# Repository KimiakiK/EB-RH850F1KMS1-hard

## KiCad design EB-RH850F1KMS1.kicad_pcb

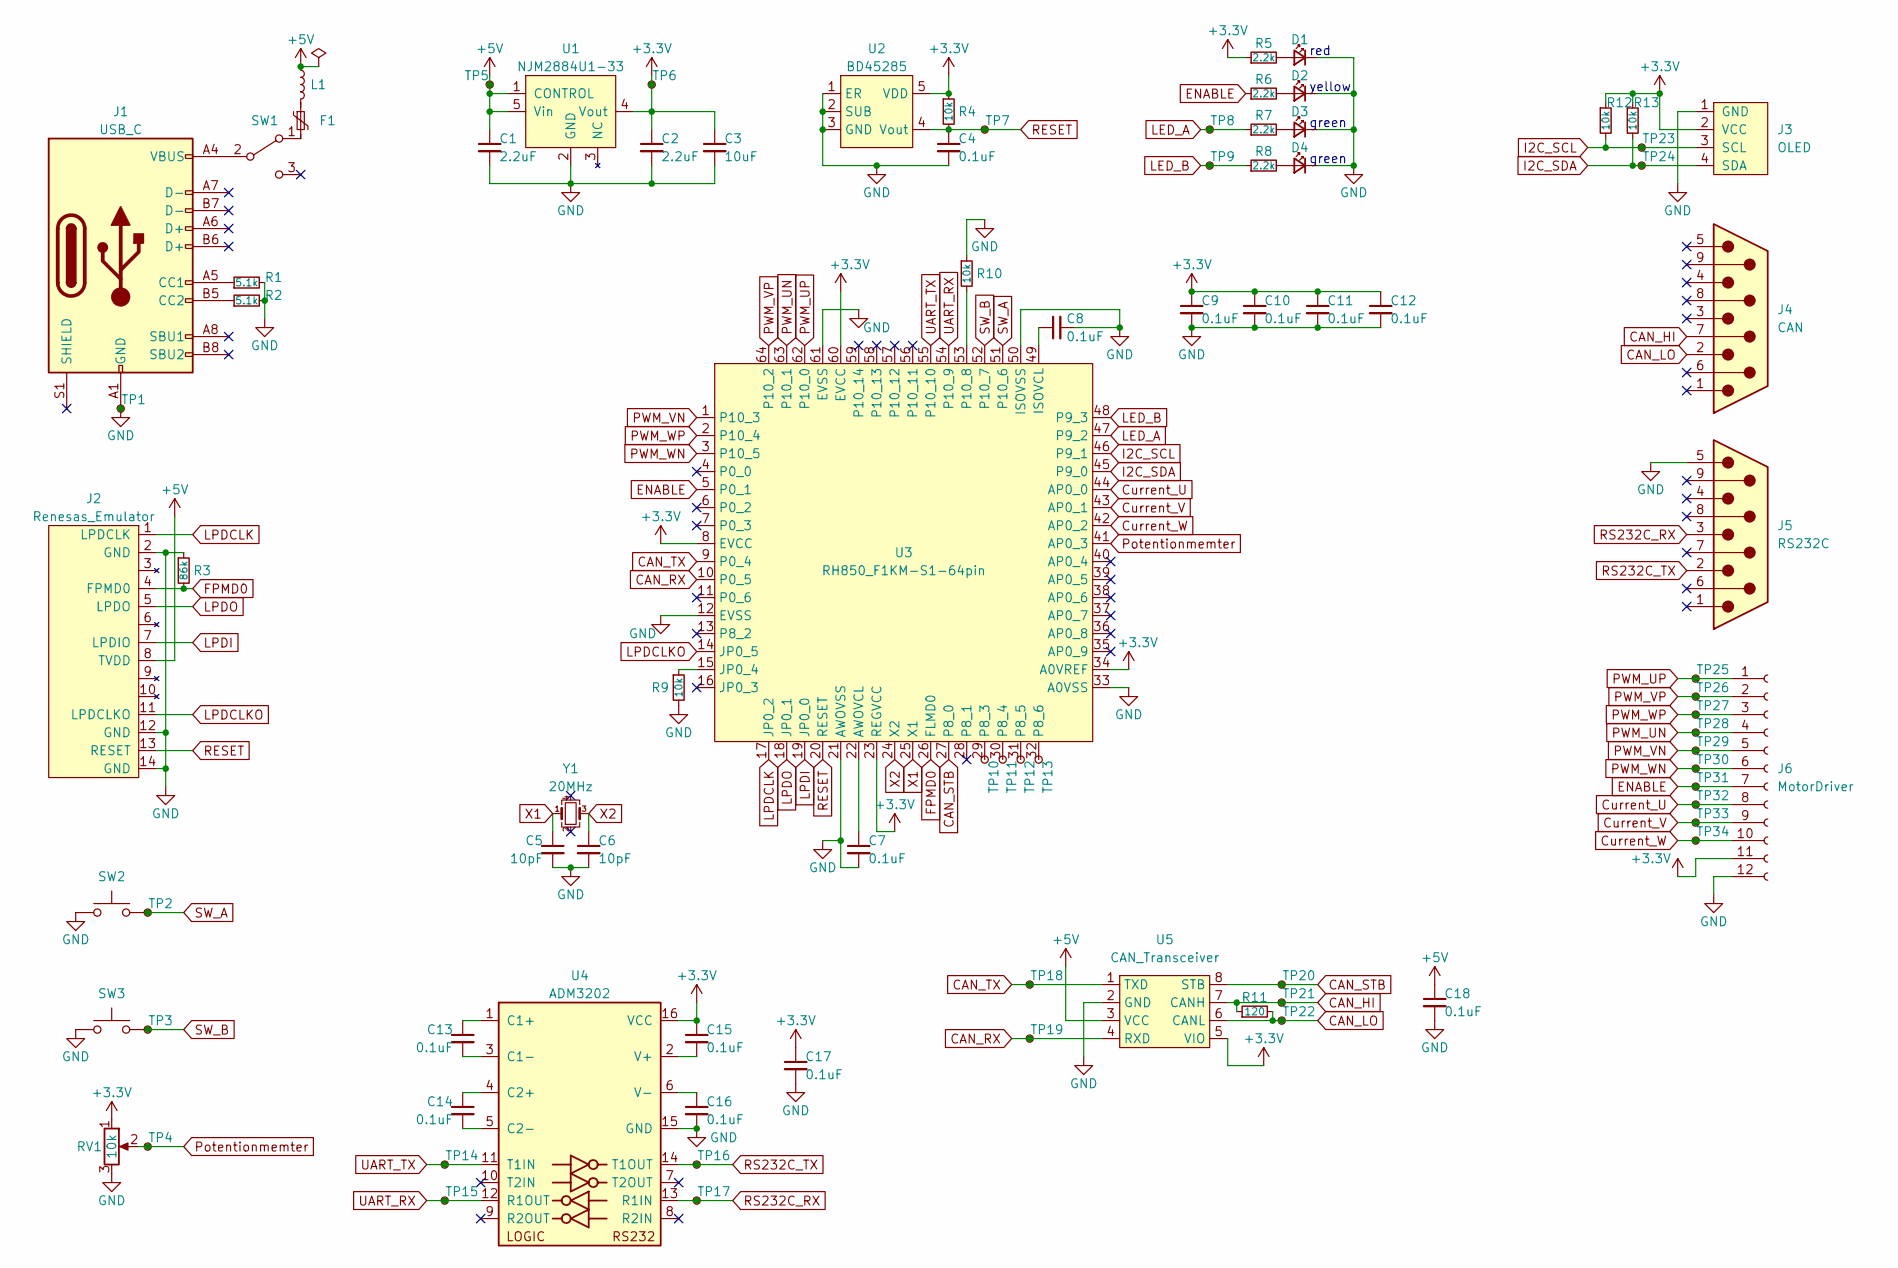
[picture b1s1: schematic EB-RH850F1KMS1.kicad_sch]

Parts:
C1, C2: 2.2uF; 1608Metric
C3: 10uF; 1608Metric
C4, C7, C8, C9, C10, C11, C12, C13, C14, C15, C16, C17, C18: 0.1uF; 1608Metric
C5, C6: 10pF; 1005Metric
D1, D2, D3, D4: LED; 1608Metric
F1: Polyfuse; 1608Metric
J1: USB_C; USB Type-C 5077CR-16SMC2-BK-TR
J2: Renesas_Emulator; IDC-Header_2x07_P2.54mm_Vertical
J3: OLED; OLED_128x64
J4: CAN; DSUB-9_Male_Horizontal_P2.77x2.84mm_EdgePinOffset7.70mm_Hou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
J5: RS232C; DSUB-9_Male_Horizontal_P2.77x2.84mm_EdgePinOffset7.70mm_Hou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
J6: MotorDriver; PinSocket_2x06_P2.54mm_Horizontal
L1: L; 1608Metric
R1, R2: 5.1k; 1608Metric
R3: 86k; 1608Metric
R4, R9, R10, R12, R13: 10k; 1608Metric
R5, R6, R7, R8: 2.2k; 1608Metric
R11: 120; 1608Metric
RV1: 10k; Potentiometer_Alps_RK097_Dual_Horizontal
SW1: SW_SPDT; Toggle_Switch
SW2, SW3: SW_Push; SW_TVAF06
TP1, TP2, TP3, TP4, TP5, TP6, TP7, TP8, TP9, TP10, TP11, TP12, TP13, TP14, TP15, TP16, TP17, TP18, TP19, TP20, TP21, TP22, TP23, TP24, TP25, TP26, TP27, TP28, TP29, TP30, TP31, TP32, TP33, TP34: TestPoint; TestPoint_Plated_Hole_D0.8mm
U1: NJM2884U1-33; SOT-89-5
U2: BD45285; SOT-23-5
U3: RH850_F1KM-S1-64pin; LQFP-64_10x10mm_P0.5mm
U4: ADM3202; TSSOP-16-1EP_4.4x5mm_P0.65mm
U5: CAN_Transceiver; DIP-8_W7.62mm_Socket
Y1: 20MHz; Crystal_SMD_3225-4Pin_3.2x2.5mm

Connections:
+3.3V: C2.1, C3.1, C9.1, C10.1, C11.1, C12.1, C15.1, C17.1, J3.2 (VCC), J6.11, R4.1, R5.1, R12.1, R13.1, RV1.1, TP6.1, U1.4 (Vout), U2.5 (VDD), U3.8 (EVCC), U3.23 (REGVCC), U3.34 (A0VREF), U3.60 (EVCC), U4.16 (VCC), U5.5 (VIO)
+5V: C1.1, C18.1, J2.8 (TVDD), L1.1, TP5.1, U1.1 (CONTROL), U1.5 (Vin), U5.3 (VCC)
CAN_HI: J4.7, R11.1, TP21.1, U5.7 (CANH)
CAN_LO: J4.2, R11.2, TP22.1, U5.6 (CANL)
CAN_RX: TP19.1, U3.10 (P0_5), U5.4 (RXD)
CAN_STB: TP20.1, U3.27 (P8_0), U5.8 (STB)
CAN_TX: TP18.1, U3.9 (P0_4), U5.1 (TXD)
Current_U: J6.8, TP32.1, U3.44 (AP0_0)
Current_V: J6.9, TP33.1, U3.43 (AP0_1)
Current_W: J6.10, TP34.1, U3.42 (AP0_2)
ENABLE: J6.7, R6.1, TP31.1, U3.5 (P0_1)
FPMD0: J2.4 (FPMD0), R3.2, U3.26 (FLMD0)
GND: C1.2, C2.2, C3.2, C4.2, C5.2, C6.2, C7.2, C8.2, C9.2, C10.2, C11.2, C12.2, C16.2, C17.2, C18.2, D1.1 (K), D2.1 (K), D3.1 (K), D4.1 (K), J1.A1 (GND), J1.A12 (GND), J1.B1 (GND), J1.B12 (GND), J2.2 (GND), J2.12 (GND), J2.14 (GND), J3.1 (GND), J5.5, J6.12, R1.2, R2.2, R3.1, R9.2, R10.1, RV1.3, SW2.1, SW3.1, TP1.1, U1.2 (GND), U2.1 (ER), U2.2 (SUB), U2.3 (GND), U3.12 (EVSS), U3.21 (AWOVSS), U3.33 (A0VSS), U3.50 (ISOVSS), U3.61 (EVSS), U4.15 (GND), U5.2 (GND)
I2C_SCL: J3.3 (SCL), R12.2, TP23.1, U3.46 (P9_1)
I2C_SDA: J3.4 (SDA), R13.2, TP24.1, U3.45 (P9_0)
LED_A: R7.1, TP8.1, U3.47 (P9_2)
LED_B: R8.1, TP9.1, U3.48 (P9_3)
LPDCLK: J2.1 (LPDCLK), U3.17 (JP0_2)
LPDCLKO: J2.11 (LPDCLKO), U3.14 (JP0_5)
LPDI: J2.7 (LPDIO), U3.19 (JP0_0)
LPDO: J2.5 (LPDO), U3.18 (JP0_1)
unnamed: D1.2 (A), R5.2
unnamed: D2.2 (A), R6.2
unnamed: D3.2 (A), R7.2
unnamed: D4.2 (A), R8.2
unnamed: F1.1, L1.2
unnamed: J1.A5 (CC1), R1.1
unnamed: J1.B5 (CC2), R2.1
unnamed: F1.2, SW1.1 (A)
unnamed: J1.A4 (VBUS), J1.A9 (VBUS), J1.B4 (VBUS), J1.B9 (VBUS), SW1.2 (B)
unnamed: C7.1, U3.22 (AWOVCL)
unnamed: C8.1, U3.49 (ISOVCL)
unnamed: R9.1, U3.15 (JP0_4)
unnamed: TP10.1, U3.29 (P8_3)
unnamed: TP11.1, U3.30 (P8_4)
unnamed: TP12.1, U3.31 (P8_5)
unnamed: TP13.1, U3.32 (P8_6)
unnamed: R10.2, U3.53 (P10_8)
unnamed: C13.1, U4.1 (C1+)
unnamed: C13.2, U4.3 (C1-)
unnamed: C14.1, U4.4 (C2+)
unnamed: C14.2, U4.5 (C2-)
unnamed: C15.2, U4.2 (V+)
unnamed: C16.1, U4.6 (V-)
PWM_UN: J6.4, TP28.1, U3.63 (P10_1)
PWM_UP: J6.1, TP25.1, U3.62 (P10_0)
PWM_VN: J6.5, TP29.1, U3.1 (P10_3)
PWM_VP: J6.2, TP26.1, U3.64 (P10_2)
PWM_WN: J6.6, TP30.1, U3.3 (P10_5)
PWM_WP: J6.3, TP27.1, U3.2 (P10_4)
Potentionmemter: RV1.2, TP4.1, U3.41 (AP0_3)
RESET: C4.1, J2.13 (RESET), R4.2, TP7.1, U2.4 (Vout), U3.20 (RESET)
RS232C_RX: J5.3, TP17.1, U4.13 (R1IN)
RS232C_TX: J5.2, TP16.1, U4.14 (T1OUT)
SW_A: SW2.2, TP2.1, U3.51 (P10_6)
SW_B: SW3.2, TP3.1, U3.52 (P10_7)
UART_RX: TP15.1, U3.54 (P10_9), U4.12 (R1OUT)
UART_TX: TP14.1, U3.55 (P10_10), U4.11 (T1IN)
X1: C5.1, U3.25 (X1), Y1.1
X2: C6.1, U3.24 (X2), Y1.3

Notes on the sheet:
green
red
yellow

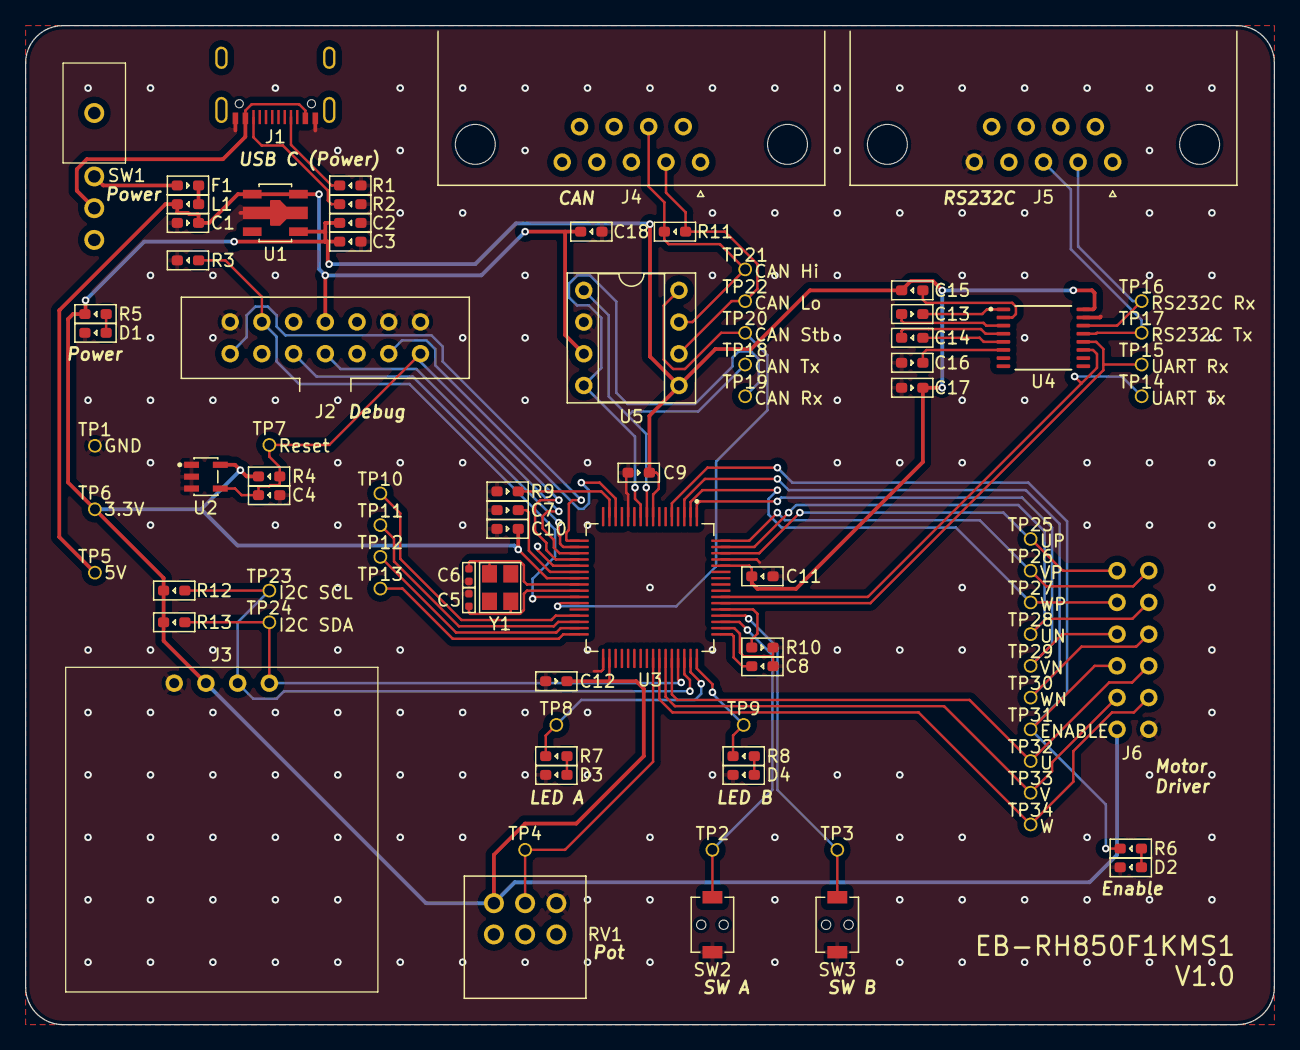
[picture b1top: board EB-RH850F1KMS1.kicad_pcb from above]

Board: 2 copper layers, 100.0 x 80.0 mm, 87 parts (0 on the bottom side), 60 nets.

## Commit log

2023-12-17 基板 V1.0
2024-01-11 回路図追加
